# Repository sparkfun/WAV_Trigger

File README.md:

WAV Trigger
===============

[*WAV Trigger (WIG-13660)*](https://www.sparkfun.com/products/13660)

The WAV Trigger is similar to its cousin, the MP3 Trigger, however it plays .WAV files and allows them to be mixed on the fly. 

This board was created in Eagle v6.0.5.

Repository Contents
-------------------

* **/Hardware** - Eagle PCB layout files (.brd, .sch)
* **/Production** - Test bed files and production panel files

Documentation
--------------
* **[Arduino Library](https://github.com/robertsonics/WAV-Trigger-Arduino-Serial-Library)** - Arduino library for the WAV Trigger.
* **[Hookup Guide](https://learn.sparkfun.com/tutorials/wav-trigger-hookup-guide-v11)** - Basic hookup guide for the WAV Trigger.

Product Versions
----------------
* [WIG-13660](https://www.sparkfun.com/products/13660) - vH1.1
* [WIG-12897](https://www.sparkfun.com/products/12897) - vH1.1
* [WIG-13660](https://www.sparkfun.com/products/12000) - vH1.0

Version History
---------------
* vH11
* vH10 - First production run.

License Information
-------------------
All contents of this repository are released under [Creative Commons Share-alike 3.0](http://creativecommons.org/licenses/by-sa/3.0/).

Authors
--------
Jamie Robertson @ robertsonics
Jordan McConnell @ SparkFun Electronics

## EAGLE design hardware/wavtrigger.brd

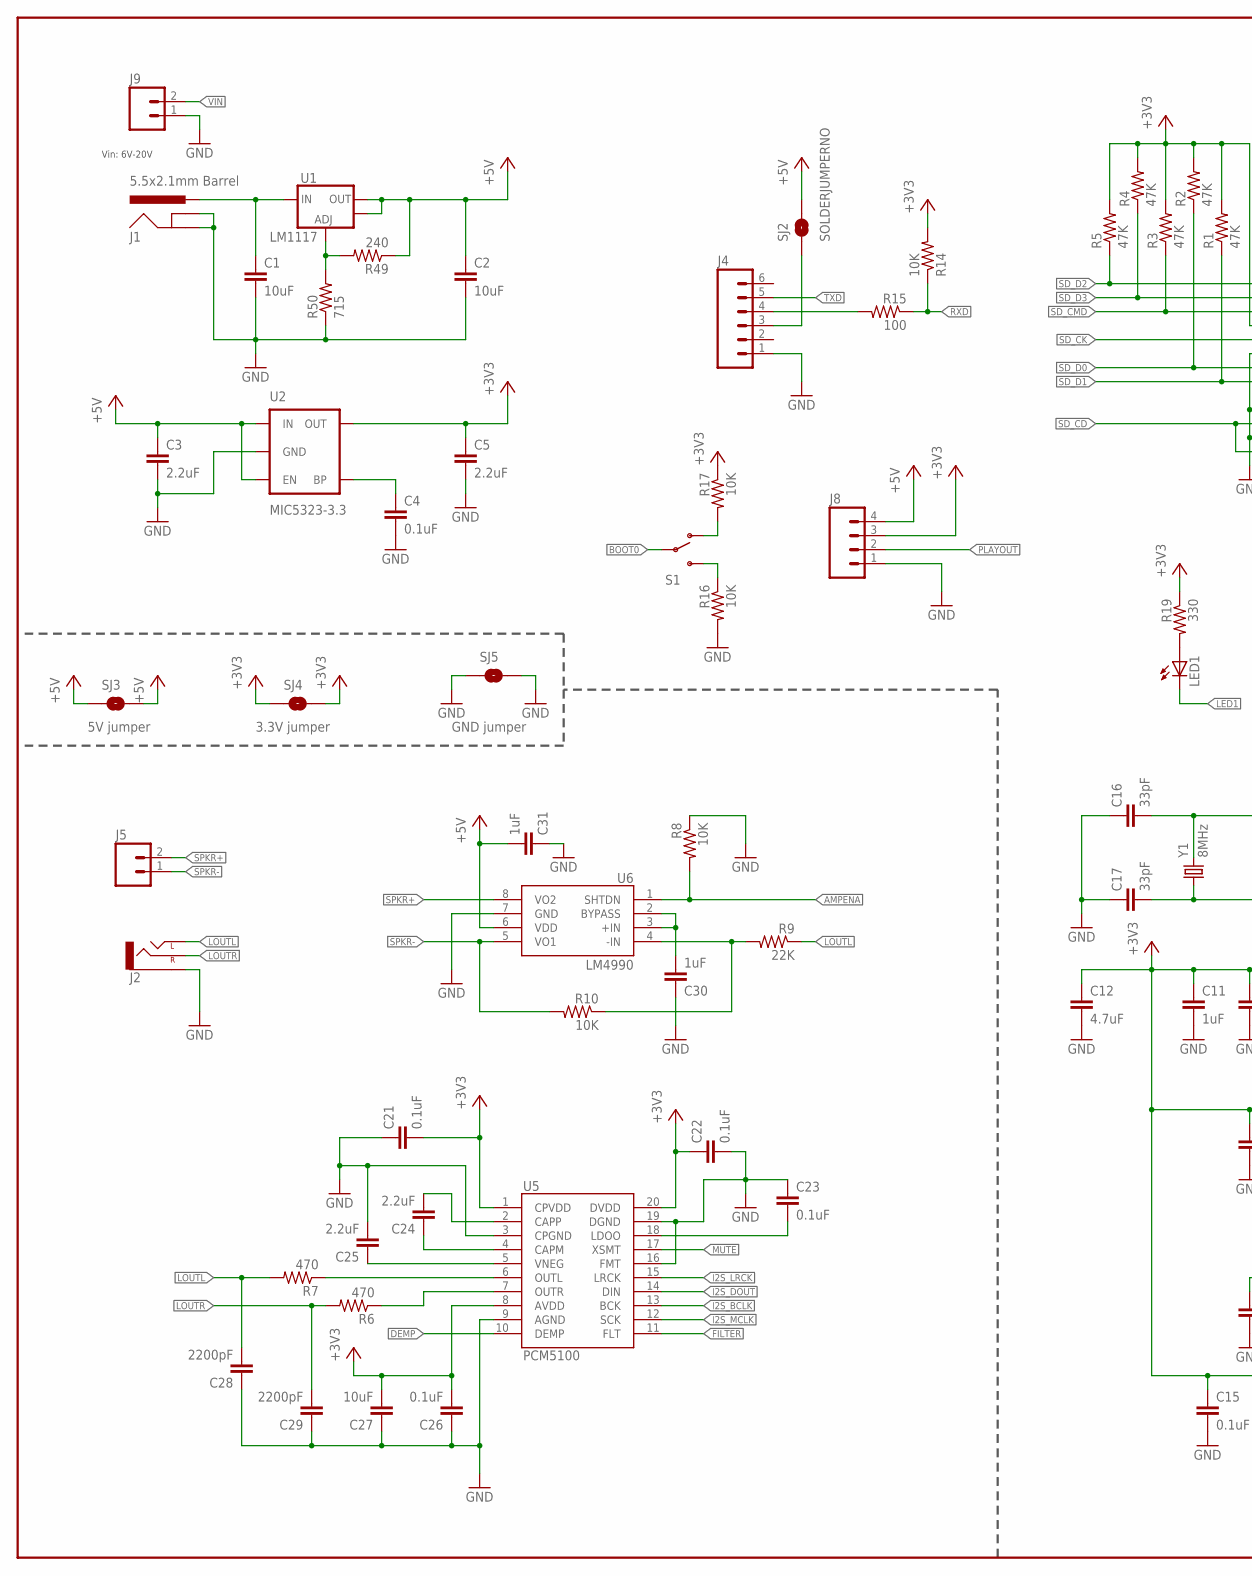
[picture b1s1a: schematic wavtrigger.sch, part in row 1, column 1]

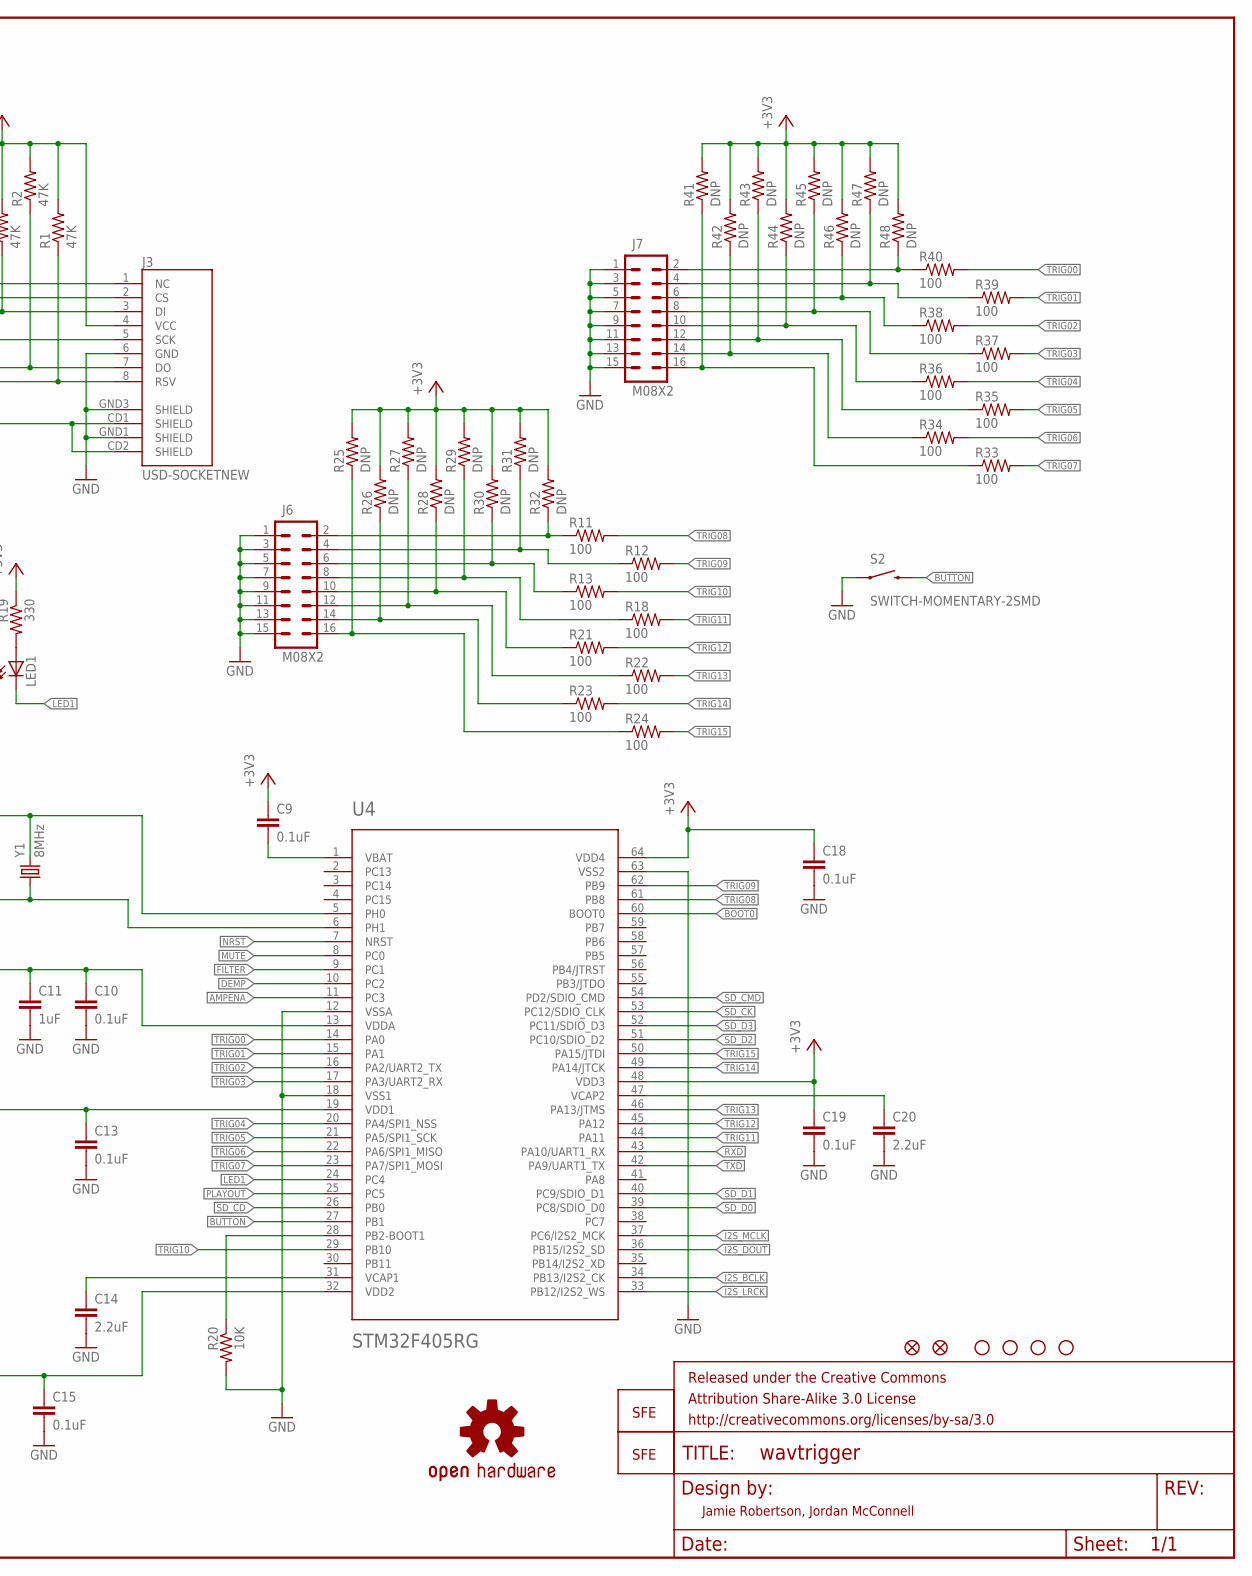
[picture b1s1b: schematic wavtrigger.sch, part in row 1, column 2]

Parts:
C1: 10uF; 1210
C2: 10uF; 0805
C3, C5: 2.2uF; 0805
C4, C9, C10, C13, C15, C18, C19, C21, C22, C23, C26: 0.1uF; 0603-CAP
C11, C30, C31: 1uF; 0603-CAP
C12: 4.7uF; 0603-CAP
C14, C20, C24, C25: 2.2uF; 0603-CAP
C16, C17: 33pF; 0603-CAP
C27: 10uF; 0603-CAP
C28, C29: 2200pF; 0603-CAP
FID1, FID2: FIDUCIAL1X2; FIDUCIAL-1X2
FRAME2: FRAME-LEDGER; CREATIVE_COMMONS
J1: 5.5x2.1mm Barrel; POWER_JACK_SMD
J2: AUDIO-JACKSMD2; AUDIO-JACK-3.5MM-SMD
J3: USD-SOCKETNEW; MICRO-SD-SOCKET-PP
J4: M06SIP; 1X06
J5, J9: M02PTH; 1X02
J6, J7: M08X2; 2X8
J8: M04PTH; 1X04
LED1: LED0603; LED-0603
LOGO1: OSHW-LOGOL; OSHW-LOGO-L
LOGO2: LOGO-SFENEW; SFE-NEW-WEBLOGO
LOGO3: LOGO-SFESK; SFE-LOGO-FLAME
R1, R2, R3, R4, R5: 47K; 0603-RES
R6, R7: 470; 0603-RES
R8, R10, R14, R16, R17, R20: 10K; 0603-RES
R9: 22K; 0603-RES
R11, R12, R13, R15, R18, R21, R22, R23, R24, R33, R34, R35, R36, R37, R38, R39, R40: 100; 0603-RES
R19: 330; 0603-RES
R25, R26, R27, R28, R29, R30, R31, R32, R41, R42, R43, R44, R45, R46, R47, R48: DNP; 0603-RES
R49: 240; 0603-RES
R50: 715; 0603-RES
S1: SWITCH-SPDT-SMD-A; SWITCH-SPST-SMD-A
S2: SWITCH-MOMENTARY-2SMD; TACTILE_SWITCH_SMD
SJ2: SOLDERJUMPERNO; SJ_2S-NO
SJ3, SJ4, SJ5: SOLDERJUMPERTRACE; SJ_2S-TRACE
STANDOFF1, STANDOFF2, STANDOFF3, STANDOFF4: STAND-OFF
U1: V_REG_LM1117SOT223; SOT223
U2: MIC5323-3.3; SOT23-5
U4: STM32F405RG; TQFP64
U5: PCM5100; PW_R-PDSO-G20
U6: LM4990; S-PDSO-G08
Y1: 8MHz; HC49UP

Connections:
+5V: C2.1, C3.1, C31.2, J8.4, R49.1, SJ2.2, SJ3.1, SJ3.2, U1.2 (OUT), U1.4 (OUT), U2.1 (IN), U2.3 (EN), U6.6 (VDD)
AMPENA: R8.2, U4.11 (PC3), U6.1 (SHTDN)
BOOT0: S1.2, U4.60 (BOOT0)
BUTTON: S2.3 (2), U4.27 (PB1)
DEMP: U4.10 (PC2), U5.10 (DEMP)
FILTER: U4.9 (PC1), U5.11 (FLT)
GND: C1.2, C2.2, C3.2, C4.2, C5.2, C10.2, C11.2, C12.2, C13.2, C14.2, C15.2, C16.1, C17.1, C18.2, C19.2, C20.2, C21.1, C22.2, C23.1, C25.2, C26.1, C27.1, C28.1, C29.1, C30.1, C31.1, J1.GND (GNDBREAK), J1.P$4 (GND), J2.SLEEVE, J3.6 (GND), J3.GND1 (SHIELD), J3.GND3 (SHIELD), J4.1, J6.1, J6.3, J6.5, J6.7, J6.9, J6.11, J6.13, J6.15, J7.1, J7.3, J7.5, J7.7, J7.9, J7.11, J7.13, J7.15, J8.1, J9.1, R8.1, R16.2, R20.2, R50.1, S2.1, SJ5.1, SJ5.2, U2.2 (GND), U4.12 (VSSA), U4.18 (VSS1), U4.63 (VSS2), U5.3 (CPGND), U5.9 (AGND), U5.16 (FMT), U5.19 (DGND), U6.7 (GND)
I2S_BCLK: U4.34 (PB13/I2S2_CK), U5.13 (BCK)
I2S_DOUT: U4.36 (PB15/I2S2_SD), U5.14 (DIN)
I2S_LRCK: U4.33 (PB12/I2S2_WS), U5.15 (LRCK)
I2S_MCLK: U4.37 (PC6/I2S2_MCK), U5.12 (SCK)
LED1: LED1.C, U4.24 (PC4)
LOUTL: C28.2, J2.TIP (LEFT), R7.2, R9.1
LOUTR: C29.2, J2.RING (RIGHT), R6.2
MUTE: U4.8 (PC0), U5.17 (XSMT)
unnamed: J6.2, R11.1, R32.1
unnamed: C4.1, U2.4 (BP)
unnamed: C9.2, U4.1 (VBAT)
unnamed: C14.1, U4.31 (VCAP1)
unnamed: C16.2, U4.5 (PH0), Y1.2
unnamed: C17.2, U4.6 (PH1), Y1.1
unnamed: R16.1, S1.3 (S)
unnamed: C20.1, U4.47 (VCAP2)
unnamed: J4.4, R15.2
unnamed: R17.2, S1.1 (O)
unnamed: LED1.A, R19.2
unnamed: R20.1, U4.28 (PB2-BOOT1)
unnamed: R49.2, R50.2, U1.1 (ADJ)
unnamed: C23.2, U5.18 (LDOO)
unnamed: R6.1, U5.7 (OUTR)
unnamed: C24.2, U5.2 (CAPP)
unnamed: C24.1, U5.4 (CAPM)
unnamed: C25.1, U5.5 (VNEG)
unnamed: R7.1, U5.6 (OUTL)
unnamed: C30.2, U6.2 (BYPASS), U6.3 (+IN)
unnamed: J6.4, R12.1, R31.1
unnamed: J6.6, R13.1, R30.1
unnamed: J6.8, R18.1, R29.1
unnamed: J6.10, R21.1, R28.1
unnamed: J6.12, R22.1, R27.1
unnamed: J6.14, R23.1, R26.1
unnamed: R9.2, R10.1, U6.4 (-IN)
unnamed: J6.16, R24.1, R25.1
unnamed: J4.3, SJ2.1
unnamed: J7.2, R40.1, R48.1
unnamed: J7.4, R39.1, R47.1
unnamed: J7.6, R38.1, R46.1
unnamed: J7.8, R37.1, R45.1
unnamed: J7.10, R36.1, R44.1
unnamed: J7.12, R35.1, R43.1
unnamed: J7.14, R34.1, R42.1
unnamed: J7.16, R33.1, R41.1
NRST: U4.7 (NRST)
PLAYOUT: J8.2, U4.25 (PC5)
RXD: R14.1, R15.1, U4.43 (PA10/UART1_RX)
SD_CD: J3.CD1 (SHIELD), J3.CD2 (SHIELD), U4.26 (PB0)
SD_CK: J3.5 (SCK), U4.53 (PC12/SDIO_CLK)
SD_CMD: J3.3 (DI), R3.1, U4.54 (PD2/SDIO_CMD)
SD_D0: J3.7 (DO), R2.1, U4.39 (PC8/SDIO_D0)
SD_D1: J3.8 (RSV), R1.1, U4.40 (PC9/SDIO_D1)
SD_D2: J3.1 (NC), R5.1, U4.51 (PC10/SDIO_D2)
SD_D3: J3.2 (CS), R4.1, U4.52 (PC11/SDIO_D3)
SPKR+: J5.2, U6.8 (VO2)
SPKR-: J5.1, R10.2, U6.5 (VO1)
TRIG00: R40.2, U4.14 (PA0)
TRIG01: R39.2, U4.15 (PA1)
TRIG02: R38.2, U4.16 (PA2/UART2_TX)
TRIG03: R37.2, U4.17 (PA3/UART2_RX)
TRIG04: R36.2, U4.20 (PA4/SPI1_NSS)
TRIG05: R35.2, U4.21 (PA5/SPI1_SCK)
TRIG06: R34.2, U4.22 (PA6/SPI1_MISO)
TRIG07: R33.2, U4.23 (PA7/SPI1_MOSI)
TRIG08: R11.2, U4.61 (PB8)
TRIG09: R12.2, U4.62 (PB9)
TRIG10: R13.2, U4.29 (PB10)
TRIG11: R18.2, U4.44 (PA11)
TRIG12: R21.2, U4.45 (PA12)
TRIG13: R22.2, U4.46 (PA13/JTMS)
TRIG14: R23.2, U4.49 (PA14/JTCK)
TRIG15: R24.2, U4.50 (PA15/JTDI)
TXD: J4.5, U4.42 (PA9/UART1_TX)
VCC: C5.1, C9.1, C10.1, C11.1, C12.1, C13.1, C15.1, C18.1, C19.1, C21.2, C22.1, C26.2, C27.2, J3.4 (VCC), J8.3, R1.2, R2.2, R3.2, R4.2, R5.2, R14.2, R17.1, R19.1, R25.2, R26.2, R27.2, R28.2, R29.2, R30.2, R31.2, R32.2, R41.2, R42.2, R43.2, R44.2, R45.2, R46.2, R47.2, R48.2, SJ4.1, SJ4.2, U2.5 (OUT), U4.13 (VDDA), U4.19 (VDD1), U4.32 (VDD2), U4.48 (VDD3), U4.64 (VDD4), U5.1 (CPVDD), U5.8 (AVDD), U5.20 (DVDD)
VIN: C1.1, J1.VIN0 (PWR), J9.2, U1.3 (IN)

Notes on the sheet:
Jamie Robertson, Jordan McConnell
5V jumper
3.3V jumper
GND jumper
LM1117
Vin: 6V-20V

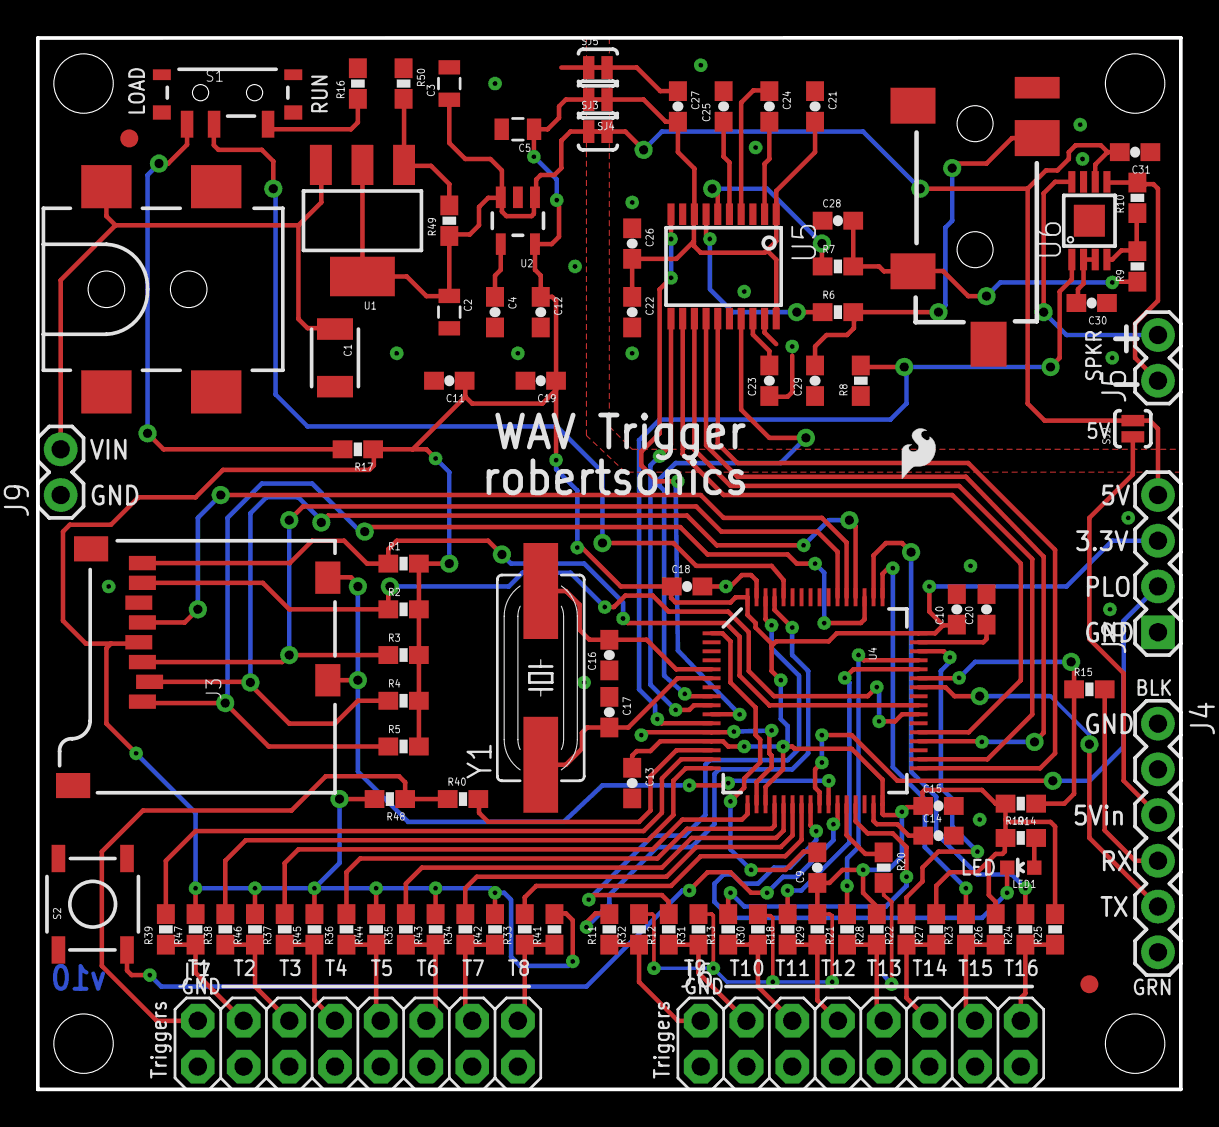
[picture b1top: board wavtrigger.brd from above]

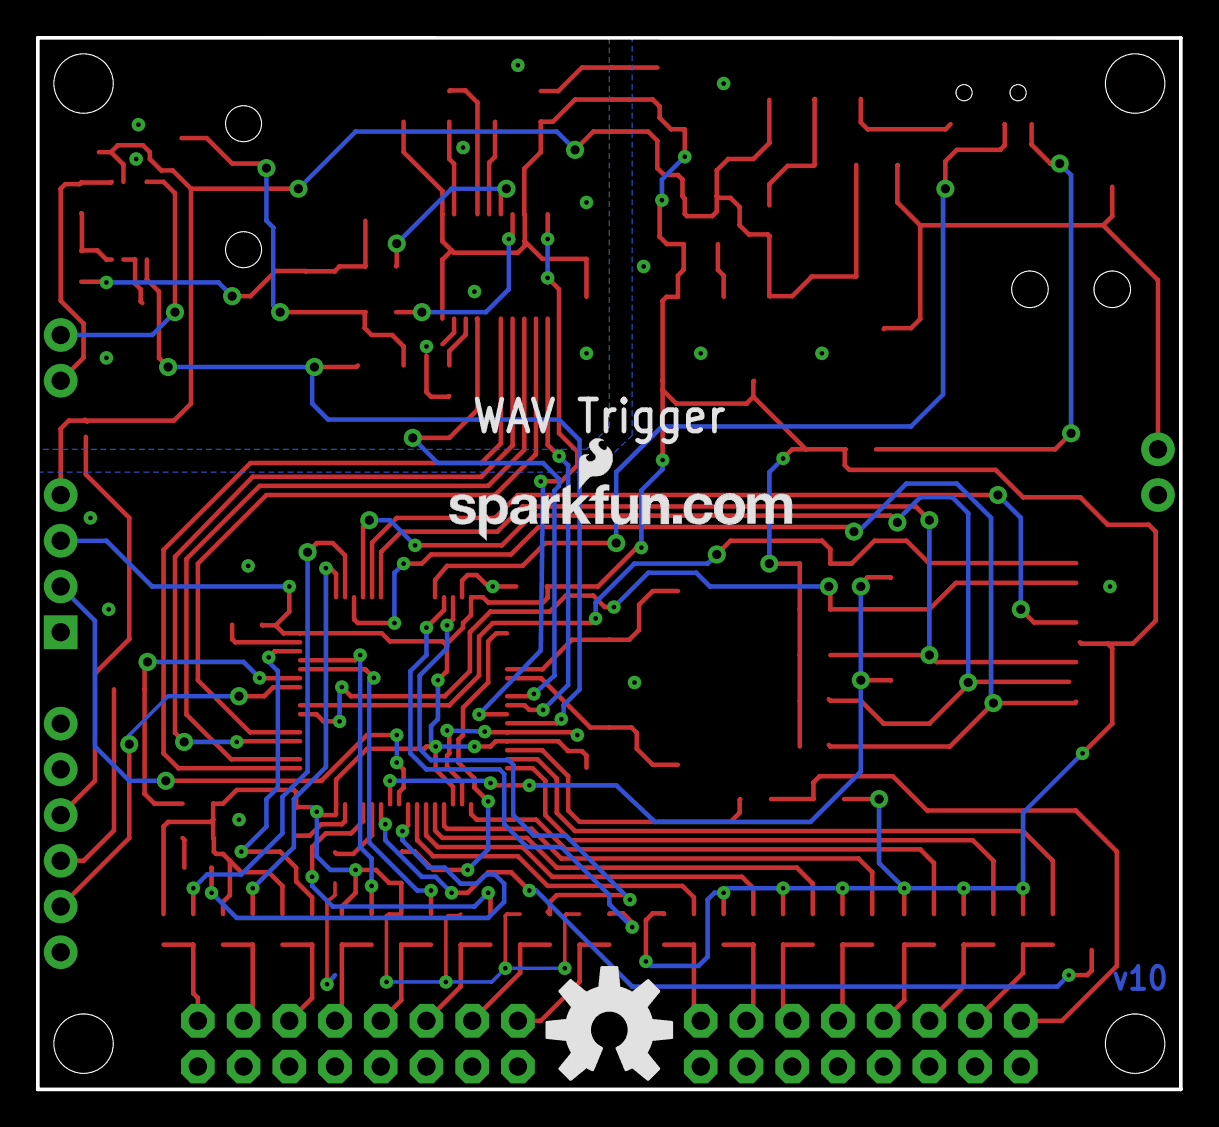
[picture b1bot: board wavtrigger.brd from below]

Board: 2 copper layers, 63.5 x 58.4 mm, 110 parts (2 on the bottom side), 82 nets.

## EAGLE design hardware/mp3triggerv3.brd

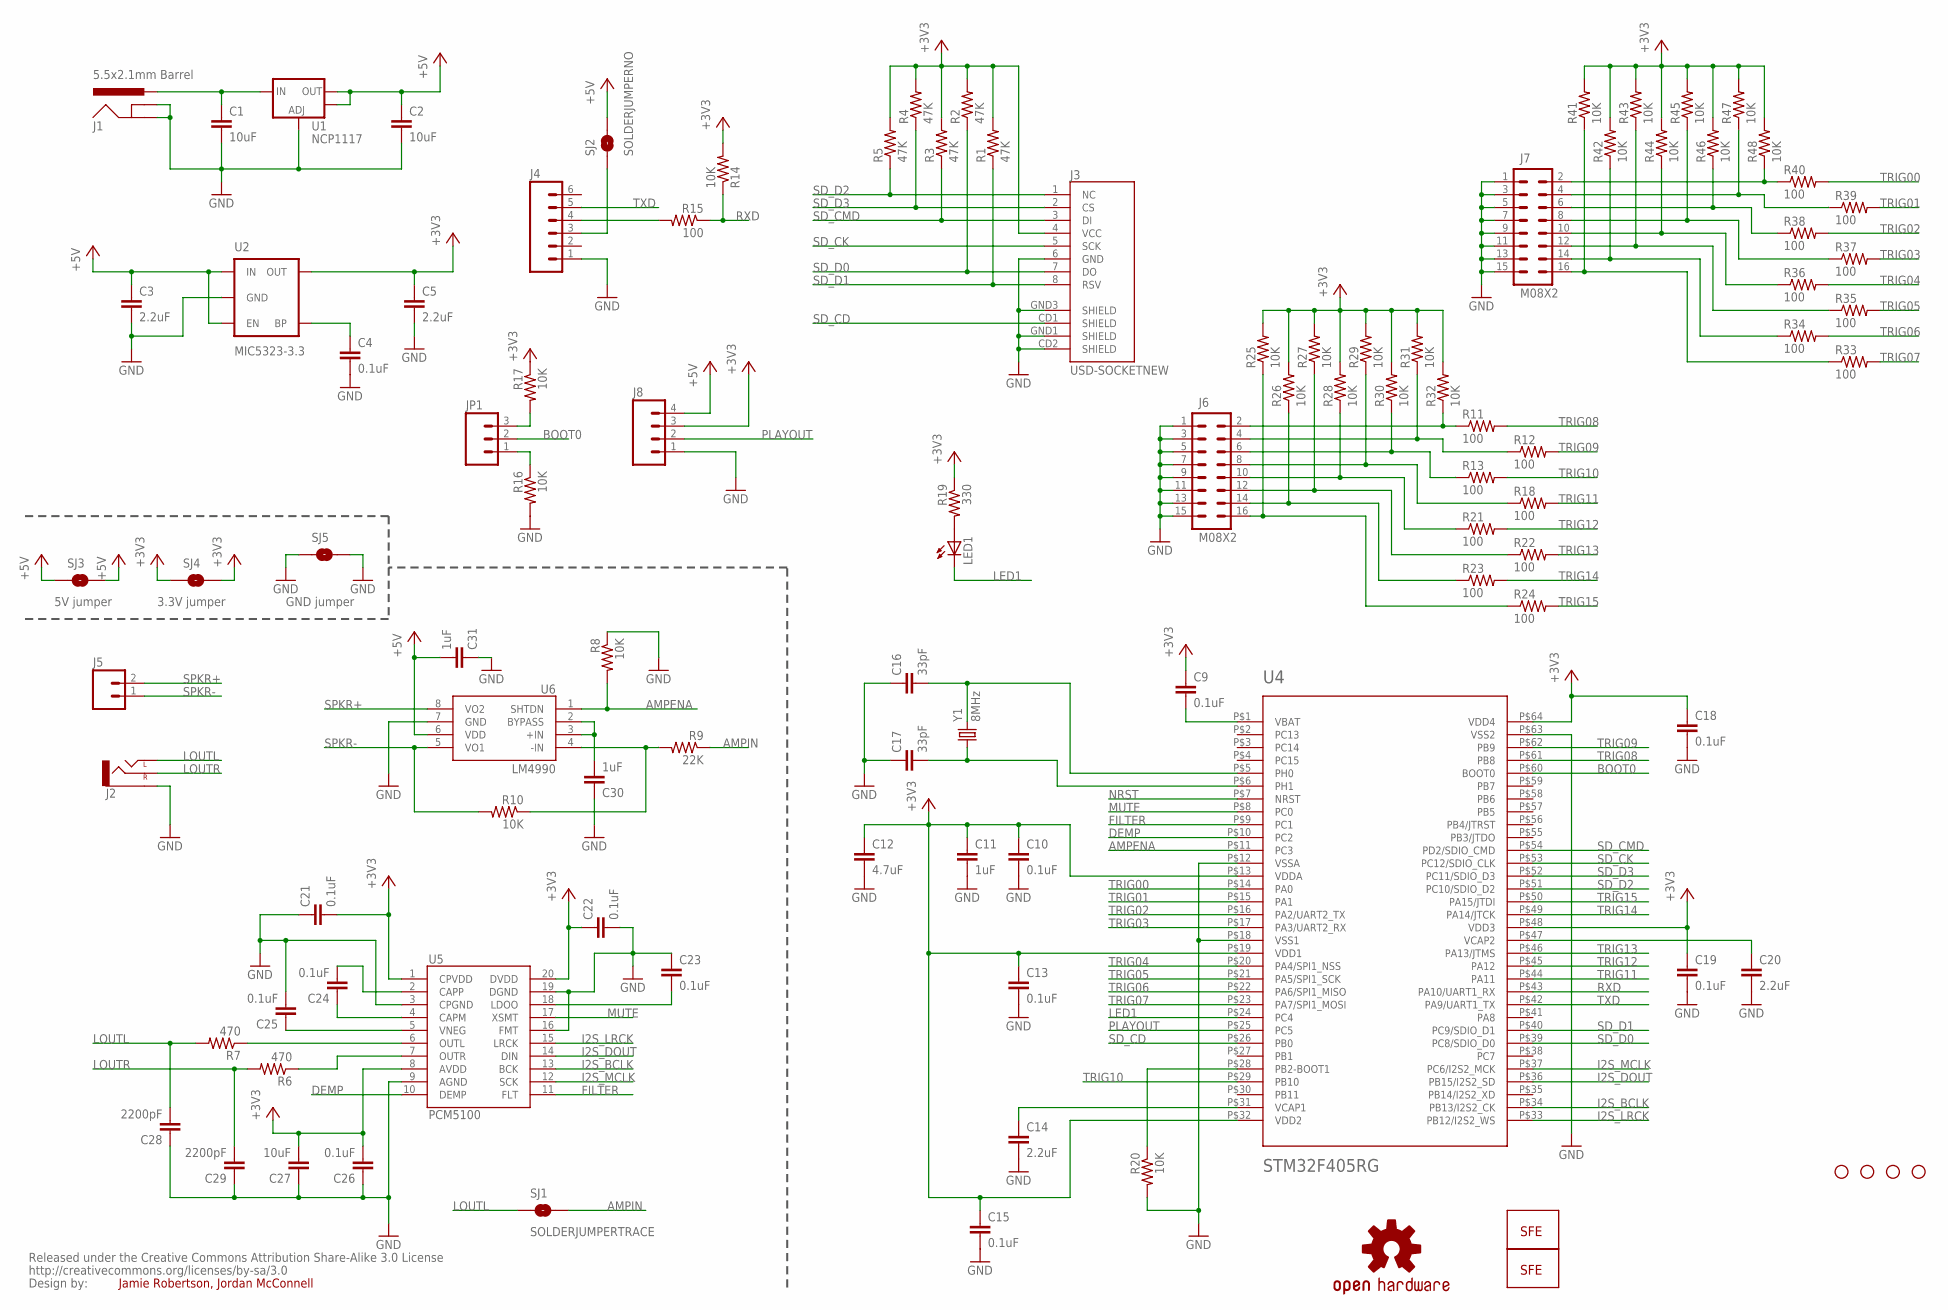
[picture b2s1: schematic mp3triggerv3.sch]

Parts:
C1: 10uF; 1210
C2: 10uF; 0805
C3, C5: 2.2uF; 0805
C4, C9, C10, C13, C15, C18, C19, C21, C22, C23, C24, C25, C26: 0.1uF; 0603-CAP
C11, C30, C31: 1uF; 0603-CAP
C12: 4.7uF; 0603-CAP
C14, C20: 2.2uF; 0603-CAP
C16, C17: 33pF; 0603-CAP
C27: 10uF; 0603-CAP
C28, C29: 2200pF; 0603-CAP
CC_TEXT1: CREATIVE_COMMONS
J1: 5.5x2.1mm Barrel; POWER_JACK_SMD
J2: AUDIO-JACKSMD2; AUDIO-JACK-3.5MM-SMD
J3: USD-SOCKETNEW; MICRO-SD-SOCKET-PP
J4: M06SIP; 1X06
J5: M02PTH; 1X02
J6, J7: M08X2; 2X8
J8: M04PTH; 1X04
JP1: M03PTH; 1X03
LED1: LED0603; LED-0603
LOGO1: OSHW-LOGOL; OSHW-LOGO-L
LOGO2: LOGO-SFENEW; SFE-NEW-WEBLOGO
LOGO3: LOGO-SFESK; SFE-LOGO-FLAME
R1, R2, R3, R4, R5: 47K; 0603-RES
R6, R7: 470; 0603-RES
R8, R10, R14, R16, R17, R20, R25, R26, R27, R28, R29, R30, R31, R32, R41, R42, R43, R44, R45, R46, R47, R48: 10K; 0603-RES
R9: 22K; 0603-RES
R11, R12, R13, R15, R18, R21, R22, R23, R24, R33, R34, R35, R36, R37, R38, R39, R40: 100; 0603-RES
R19: 330; 0603-RES
SJ1, SJ3, SJ4, SJ5: SOLDERJUMPERTRACE; SJ_2S-TRACE
SJ2: SOLDERJUMPERNO; SJ_2S-NO
STANDOFF1, STANDOFF2, STANDOFF3, STANDOFF4: STAND-OFF
U1: NCP1117; SOT223
U2: MIC5323-3.3; SOT23-5
U4: STM32F405RG; TQFP-10X10-64
U5: PCM5100; PW_R-PDSO-G20
U6: LM4990; S-PDSO-G08
Y1: 8MHz; HC49UP

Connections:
+5V: C2.1, C3.1, C31.2, J8.4, SJ2.2, SJ3.1, SJ3.2, U1.2 (OUT), U1.4 (OUT), U2.1 (IN), U2.3 (EN), U6.6 (VDD)
AMPENA: R8.2, U4.P$11 (PC3), U6.1 (SHTDN)
AMPIN: R9.1, SJ1.2
BOOT0: JP1.2, U4.P$60 (BOOT0)
DEMP: U4.P$10 (PC2), U5.10 (DEMP)
FILTER: U4.P$9 (PC1), U5.11 (FLT)
GND: C1.2, C2.2, C3.2, C4.2, C5.2, C10.2, C11.2, C12.2, C13.2, C14.2, C15.2, C16.1, C17.1, C18.2, C19.2, C20.2, C21.1, C22.2, C23.1, C25.2, C26.1, C27.1, C28.1, C29.1, C30.1, C31.1, J1.GND (GNDBREAK), J1.P$4 (GND), J2.SLEEVE, J3.6 (GND), J3.CD2 (SHIELD), J3.GND1 (SHIELD), J3.GND3 (SHIELD), J4.1, J6.1, J6.3, J6.5, J6.7, J6.9, J6.11, J6.13, J6.15, J7.1, J7.3, J7.5, J7.7, J7.9, J7.11, J7.13, J7.15, J8.1, R8.1, R16.2, R20.2, SJ5.1, SJ5.2, U1.1 (ADJ), U2.2 (GND), U4.P$12 (VSSA), U4.P$18 (VSS1), U4.P$63 (VSS2), U5.3 (CPGND), U5.9 (AGND), U5.16 (FMT), U5.19 (DGND), U6.7 (GND)
I2S_BCLK: U4.P$34 (PB13/I2S2_CK), U5.13 (BCK)
I2S_DOUT: U4.P$36 (PB15/I2S2_SD), U5.14 (DIN)
I2S_LRCK: U4.P$33 (PB12/I2S2_WS), U5.15 (LRCK)
I2S_MCLK: U4.P$37 (PC6/I2S2_MCK), U5.12 (SCK)
LED1: LED1.C, U4.P$24 (PC4)
LOUTL: C28.2, J2.TIP (LEFT), R7.2, SJ1.1
LOUTR: C29.2, J2.RING (RIGHT), R6.2
MUTE: U4.P$8 (PC0), U5.17 (XSMT)
unnamed: J6.2, R11.1, R32.1
unnamed: C4.1, U2.4 (BP)
unnamed: C9.2, U4.P$1 (VBAT)
unnamed: C14.1, U4.P$31 (VCAP1)
unnamed: C16.2, U4.P$5 (PH0), Y1.2
unnamed: C17.2, U4.P$6 (PH1), Y1.1
unnamed: JP1.1, R16.1
unnamed: C20.1, U4.P$47 (VCAP2)
unnamed: J4.4, R15.2
unnamed: JP1.3, R17.2
unnamed: LED1.A, R19.2
unnamed: R20.1, U4.P$28 (PB2-BOOT1)
unnamed: C23.2, U5.18 (LDOO)
unnamed: R6.1, U5.7 (OUTR)
unnamed: C24.2, U5.2 (CAPP)
unnamed: C24.1, U5.4 (CAPM)
unnamed: C25.1, U5.5 (VNEG)
unnamed: R7.1, U5.6 (OUTL)
unnamed: C30.2, U6.2 (BYPASS), U6.3 (+IN)
unnamed: J6.4, R12.1, R31.1
unnamed: J6.6, R13.1, R30.1
unnamed: J6.8, R18.1, R29.1
unnamed: J6.10, R21.1, R28.1
unnamed: J6.12, R22.1, R27.1
unnamed: J6.14, R23.1, R26.1
unnamed: R9.2, R10.1, U6.4 (-IN)
unnamed: J6.16, R24.1, R25.1
unnamed: J4.3, SJ2.1
unnamed: J7.2, R40.1, R48.1
unnamed: J7.4, R39.1, R47.1
unnamed: J7.6, R38.1, R46.1
unnamed: J7.8, R37.1, R45.1
unnamed: J7.10, R36.1, R44.1
unnamed: J7.12, R35.1, R43.1
unnamed: J7.14, R34.1, R42.1
unnamed: J7.16, R33.1, R41.1
NRST: U4.P$7 (NRST)
PLAYOUT: J8.2, U4.P$25 (PC5)
RXD: R14.1, R15.1, U4.P$43 (PA10/UART1_RX)
SD_CD: J3.CD1 (SHIELD), U4.P$26 (PB0)
SD_CK: J3.5 (SCK), U4.P$53 (PC12/SDIO_CLK)
SD_CMD: J3.3 (DI), R3.1, U4.P$54 (PD2/SDIO_CMD)
SD_D0: J3.7 (DO), R2.1, U4.P$39 (PC8/SDIO_D0)
SD_D1: J3.8 (RSV), R1.1, U4.P$40 (PC9/SDIO_D1)
SD_D2: J3.1 (NC), R5.1, U4.P$51 (PC10/SDIO_D2)
SD_D3: J3.2 (CS), R4.1, U4.P$52 (PC11/SDIO_D3)
SPKR+: J5.2, U6.8 (VO2)
SPKR-: J5.1, R10.2, U6.5 (VO1)
TRIG00: R40.2, U4.P$14 (PA0)
TRIG01: R39.2, U4.P$15 (PA1)
TRIG02: R38.2, U4.P$16 (PA2/UART2_TX)
TRIG03: R37.2, U4.P$17 (PA3/UART2_RX)
TRIG04: R36.2, U4.P$20 (PA4/SPI1_NSS)
TRIG05: R35.2, U4.P$21 (PA5/SPI1_SCK)
TRIG06: R34.2, U4.P$22 (PA6/SPI1_MISO)
TRIG07: R33.2, U4.P$23 (PA7/SPI1_MOSI)
TRIG08: R11.2, U4.P$61 (PB8)
TRIG09: R12.2, U4.P$62 (PB9)
TRIG10: R13.2, U4.P$29 (PB10)
TRIG11: R18.2, U4.P$44 (PA11)
TRIG12: R21.2, U4.P$45 (PA12)
TRIG13: R22.2, U4.P$46 (PA13/JTMS)
TRIG14: R23.2, U4.P$49 (PA14/JTCK)
TRIG15: R24.2, U4.P$50 (PA15/JTDI)
TXD: J4.5, U4.P$42 (PA9/UART1_TX)
VCC: C5.1, C9.1, C10.1, C11.1, C12.1, C13.1, C15.1, C18.1, C19.1, C21.2, C22.1, C26.2, C27.2, J3.4 (VCC), J8.3, R1.2, R2.2, R3.2, R4.2, R5.2, R14.2, R17.1, R19.1, R25.2, R26.2, R27.2, R28.2, R29.2, R30.2, R31.2, R32.2, R41.2, R42.2, R43.2, R44.2, R45.2, R46.2, R47.2, R48.2, SJ4.1, SJ4.2, U2.5 (OUT), U4.P$13 (VDDA), U4.P$19 (VDD1), U4.P$32 (VDD2), U4.P$48 (VDD3), U4.P$64 (VDD4), U5.1 (CPVDD), U5.8 (AVDD), U5.20 (DVDD)
VIN_9V: C1.1, J1.VIN0 (PWR), U1.3 (IN)

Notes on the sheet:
Jamie Robertson, Jordan McConnell
5V jumper
3.3V jumper
GND jumper

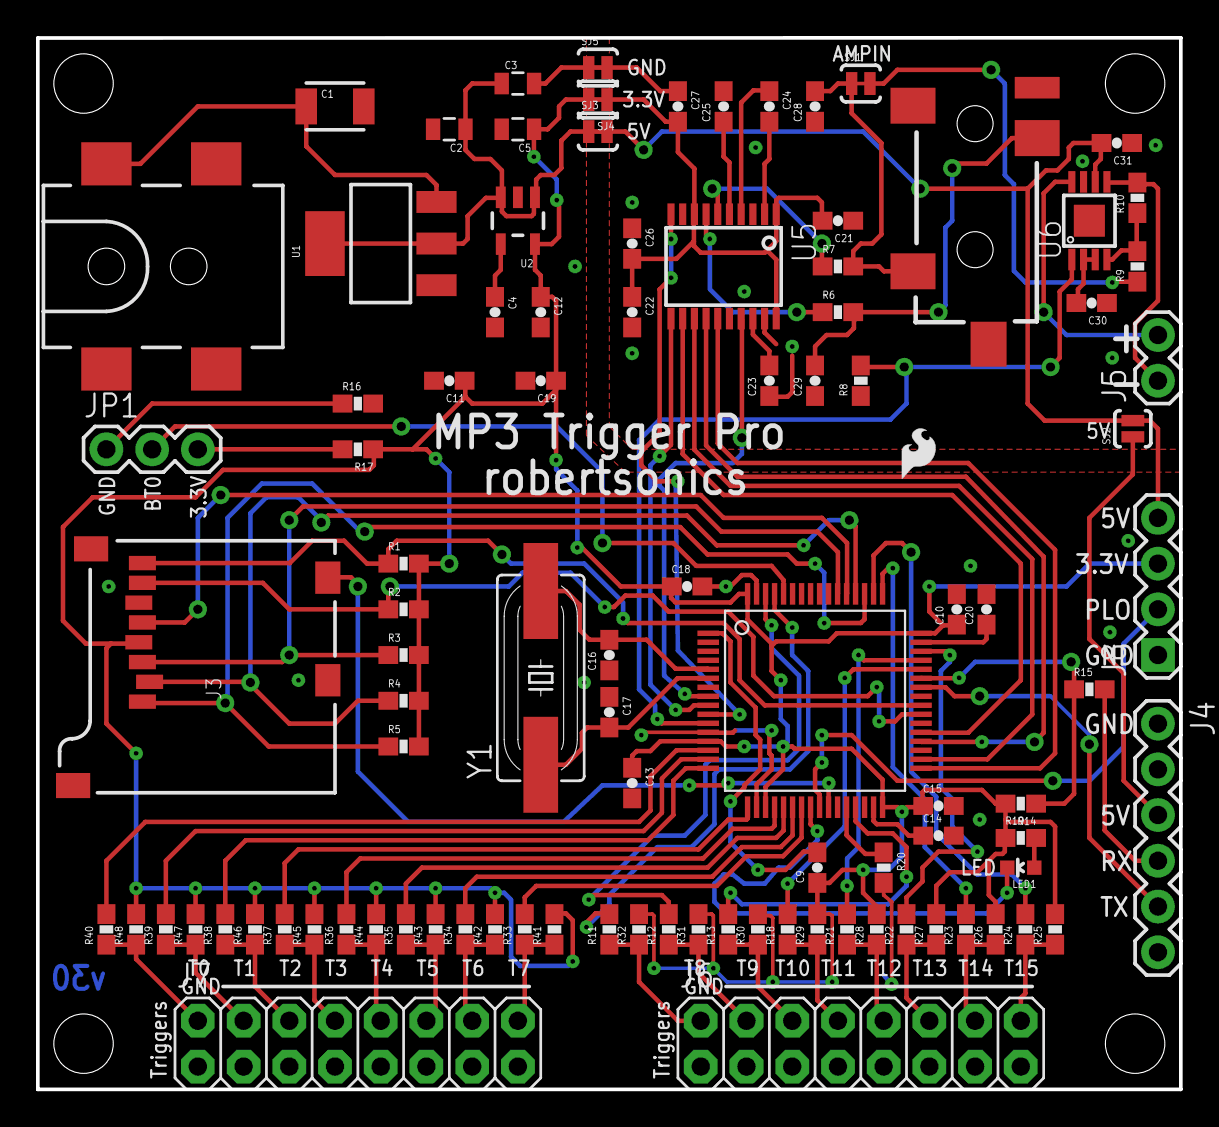
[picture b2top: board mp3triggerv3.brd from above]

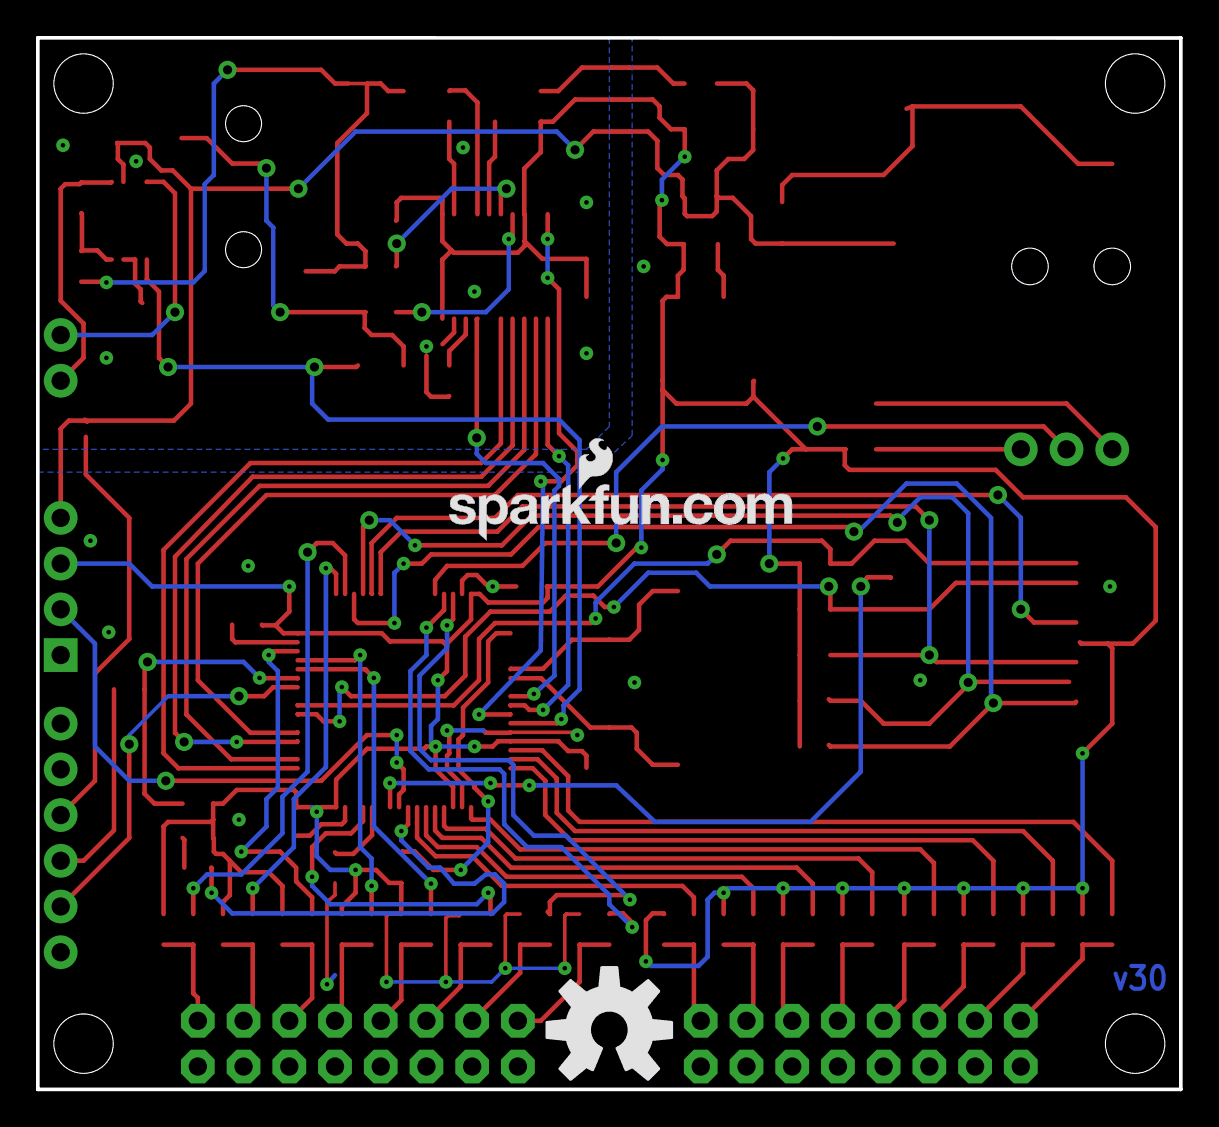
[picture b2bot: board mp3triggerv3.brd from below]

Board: 2 copper layers, 63.5 x 58.4 mm, 105 parts (2 on the bottom side), 81 nets.

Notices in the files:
parts and their libraries:
SparkFun-Connectors: Licensing: CC v3.0 Share-Alike You are welcome to use this library for commercial purposes.
SparkFun-Retired: Licensing:Creative Commons ShareAlike 4.0 International - https://creativecommons.org/licenses/by-sa/4.0
SparkFun-Aesthetics: Creative Commons License summary
